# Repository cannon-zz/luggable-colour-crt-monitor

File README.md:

# Colour CRT Monitor for a Retro Luggable Computer

I'm in the process of assembling a luggable Apple ][ clone system.  This is the colour monitor part of the project.

This monitor started out as a SKYTEK brand SCT-1024 portable colour television from May of 1988 that I picked up from an auction site.  The video baseband and CRT driver section is built around a Panasonic 150CHB22 picture tube driven by a Toshiba TA7698AP video-chroma-deflection system all-in-one chip.  I think those picture tubes were quite common in small televisions of this type, and the all-in-one chip is easy to find, so this project might be useful for others looking for a way to make a small DIY CRT colour monitor from salvaged parts.

## Status

- [X] First pass through the circuit, entering it into kicad.
  - CRT socket board not included.  Will reuse as-is.
  - 11 V regulator circuit not included.  Considering alternatives.
- [X] Remove components from PCB, confirm values out-of-circuit.
  - Confirm internal structure of flyback.
  - Identify coils, diodes, capacitors.
- [X] Select new replacement parts.
- [X] Assign footprints.
- [X] Layout PCB.
- [X] Parts and PCBs ordered.
- [ ] Assembled.
- [ ] Tested and working (knock on wood).

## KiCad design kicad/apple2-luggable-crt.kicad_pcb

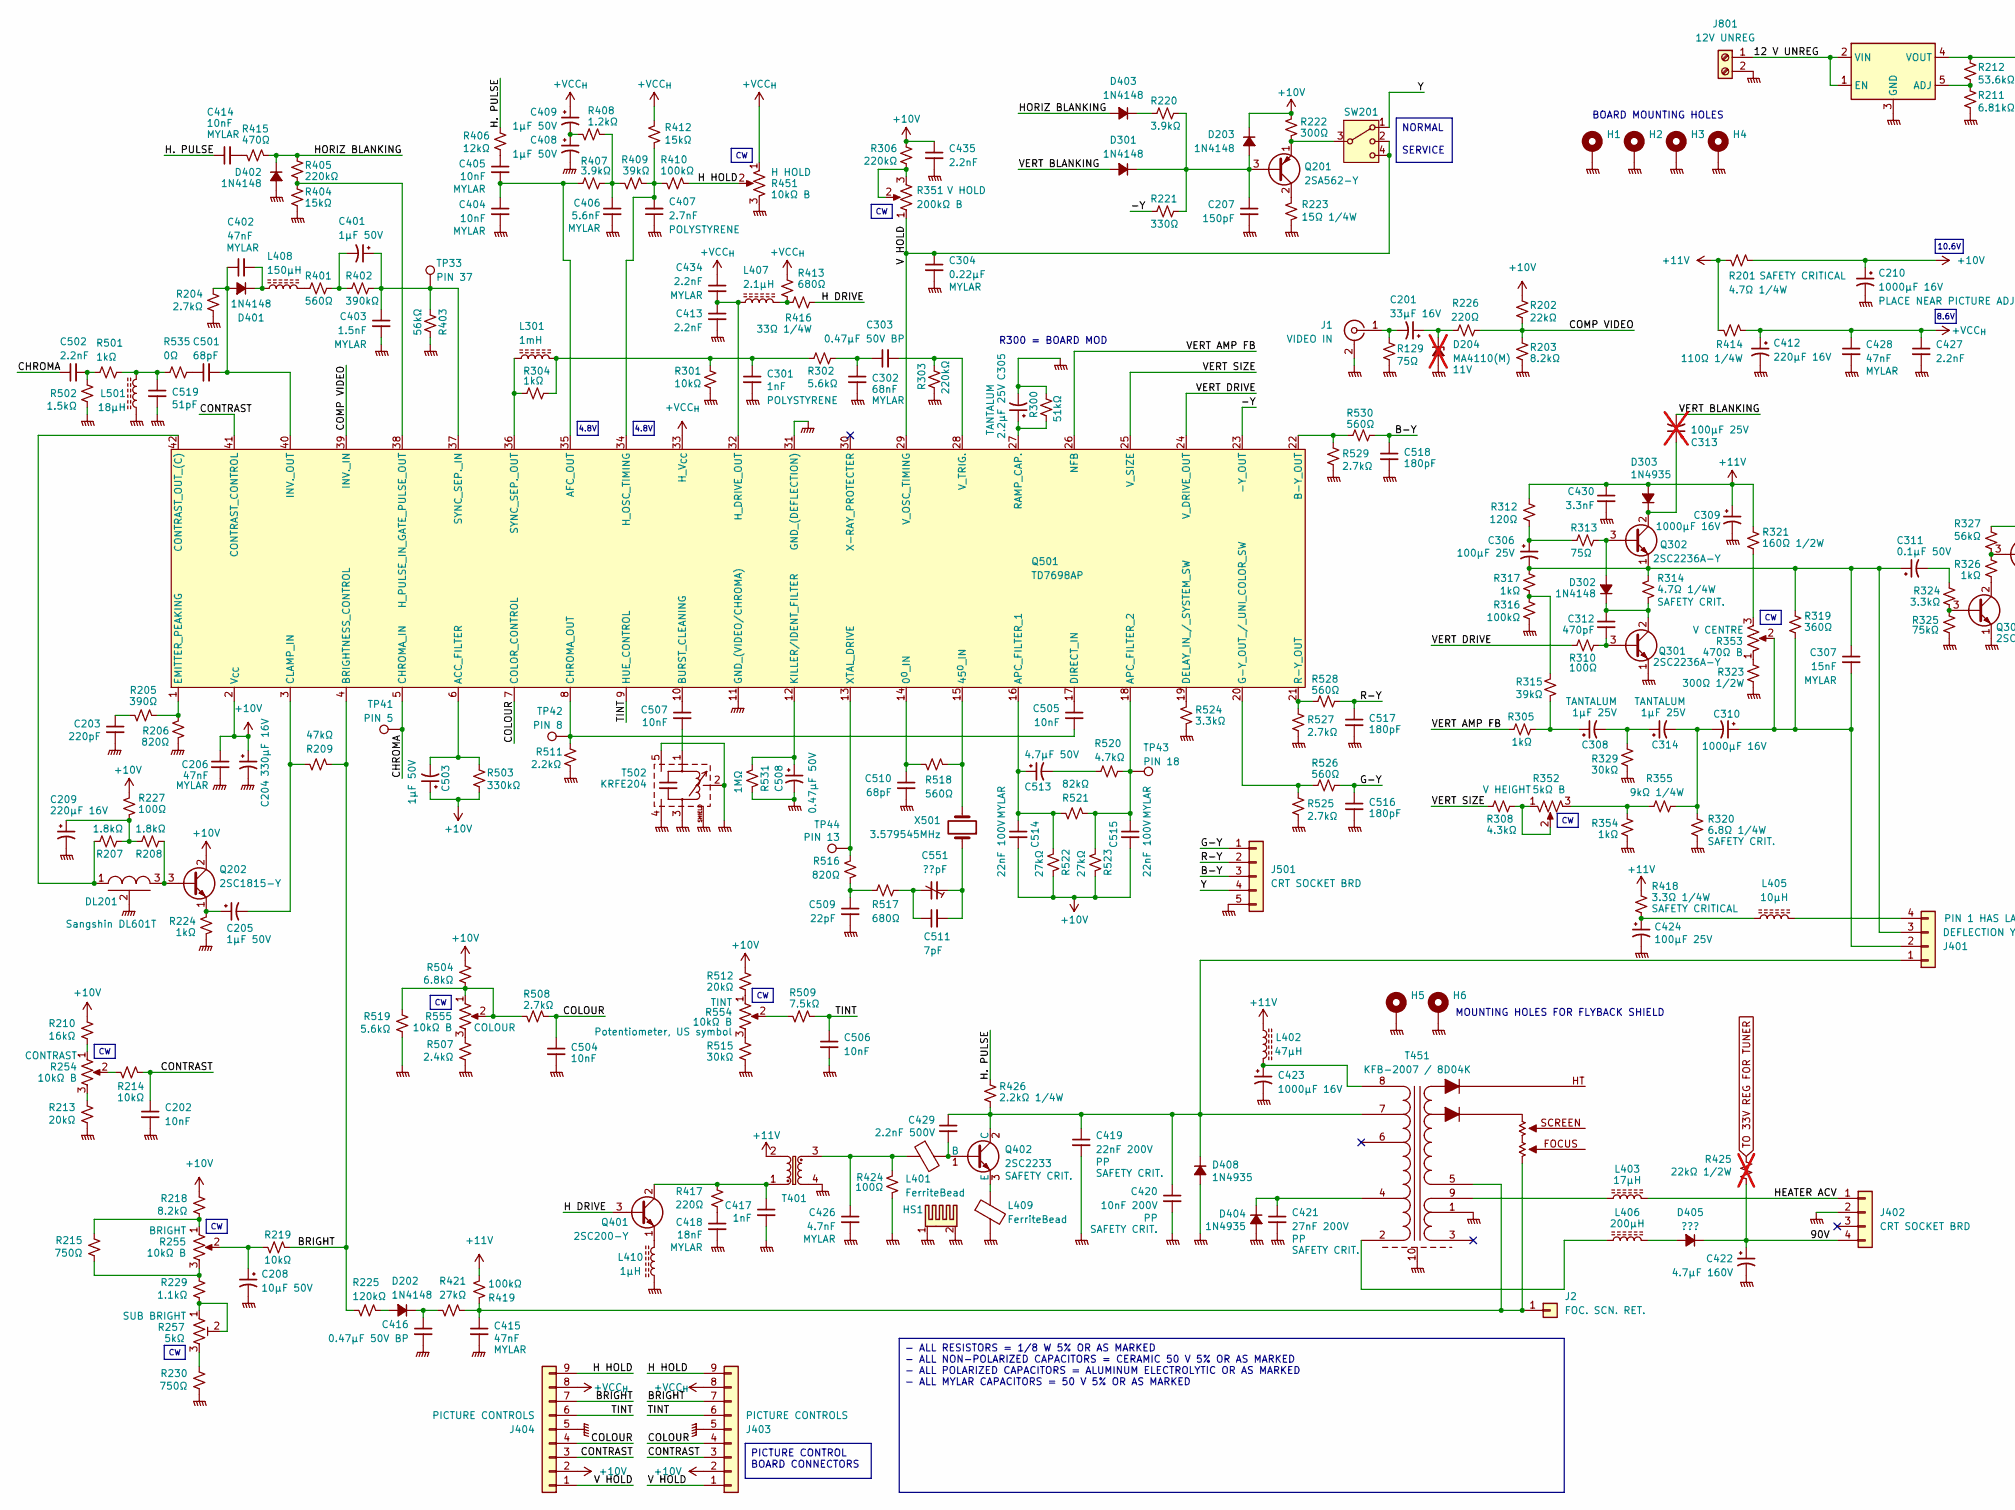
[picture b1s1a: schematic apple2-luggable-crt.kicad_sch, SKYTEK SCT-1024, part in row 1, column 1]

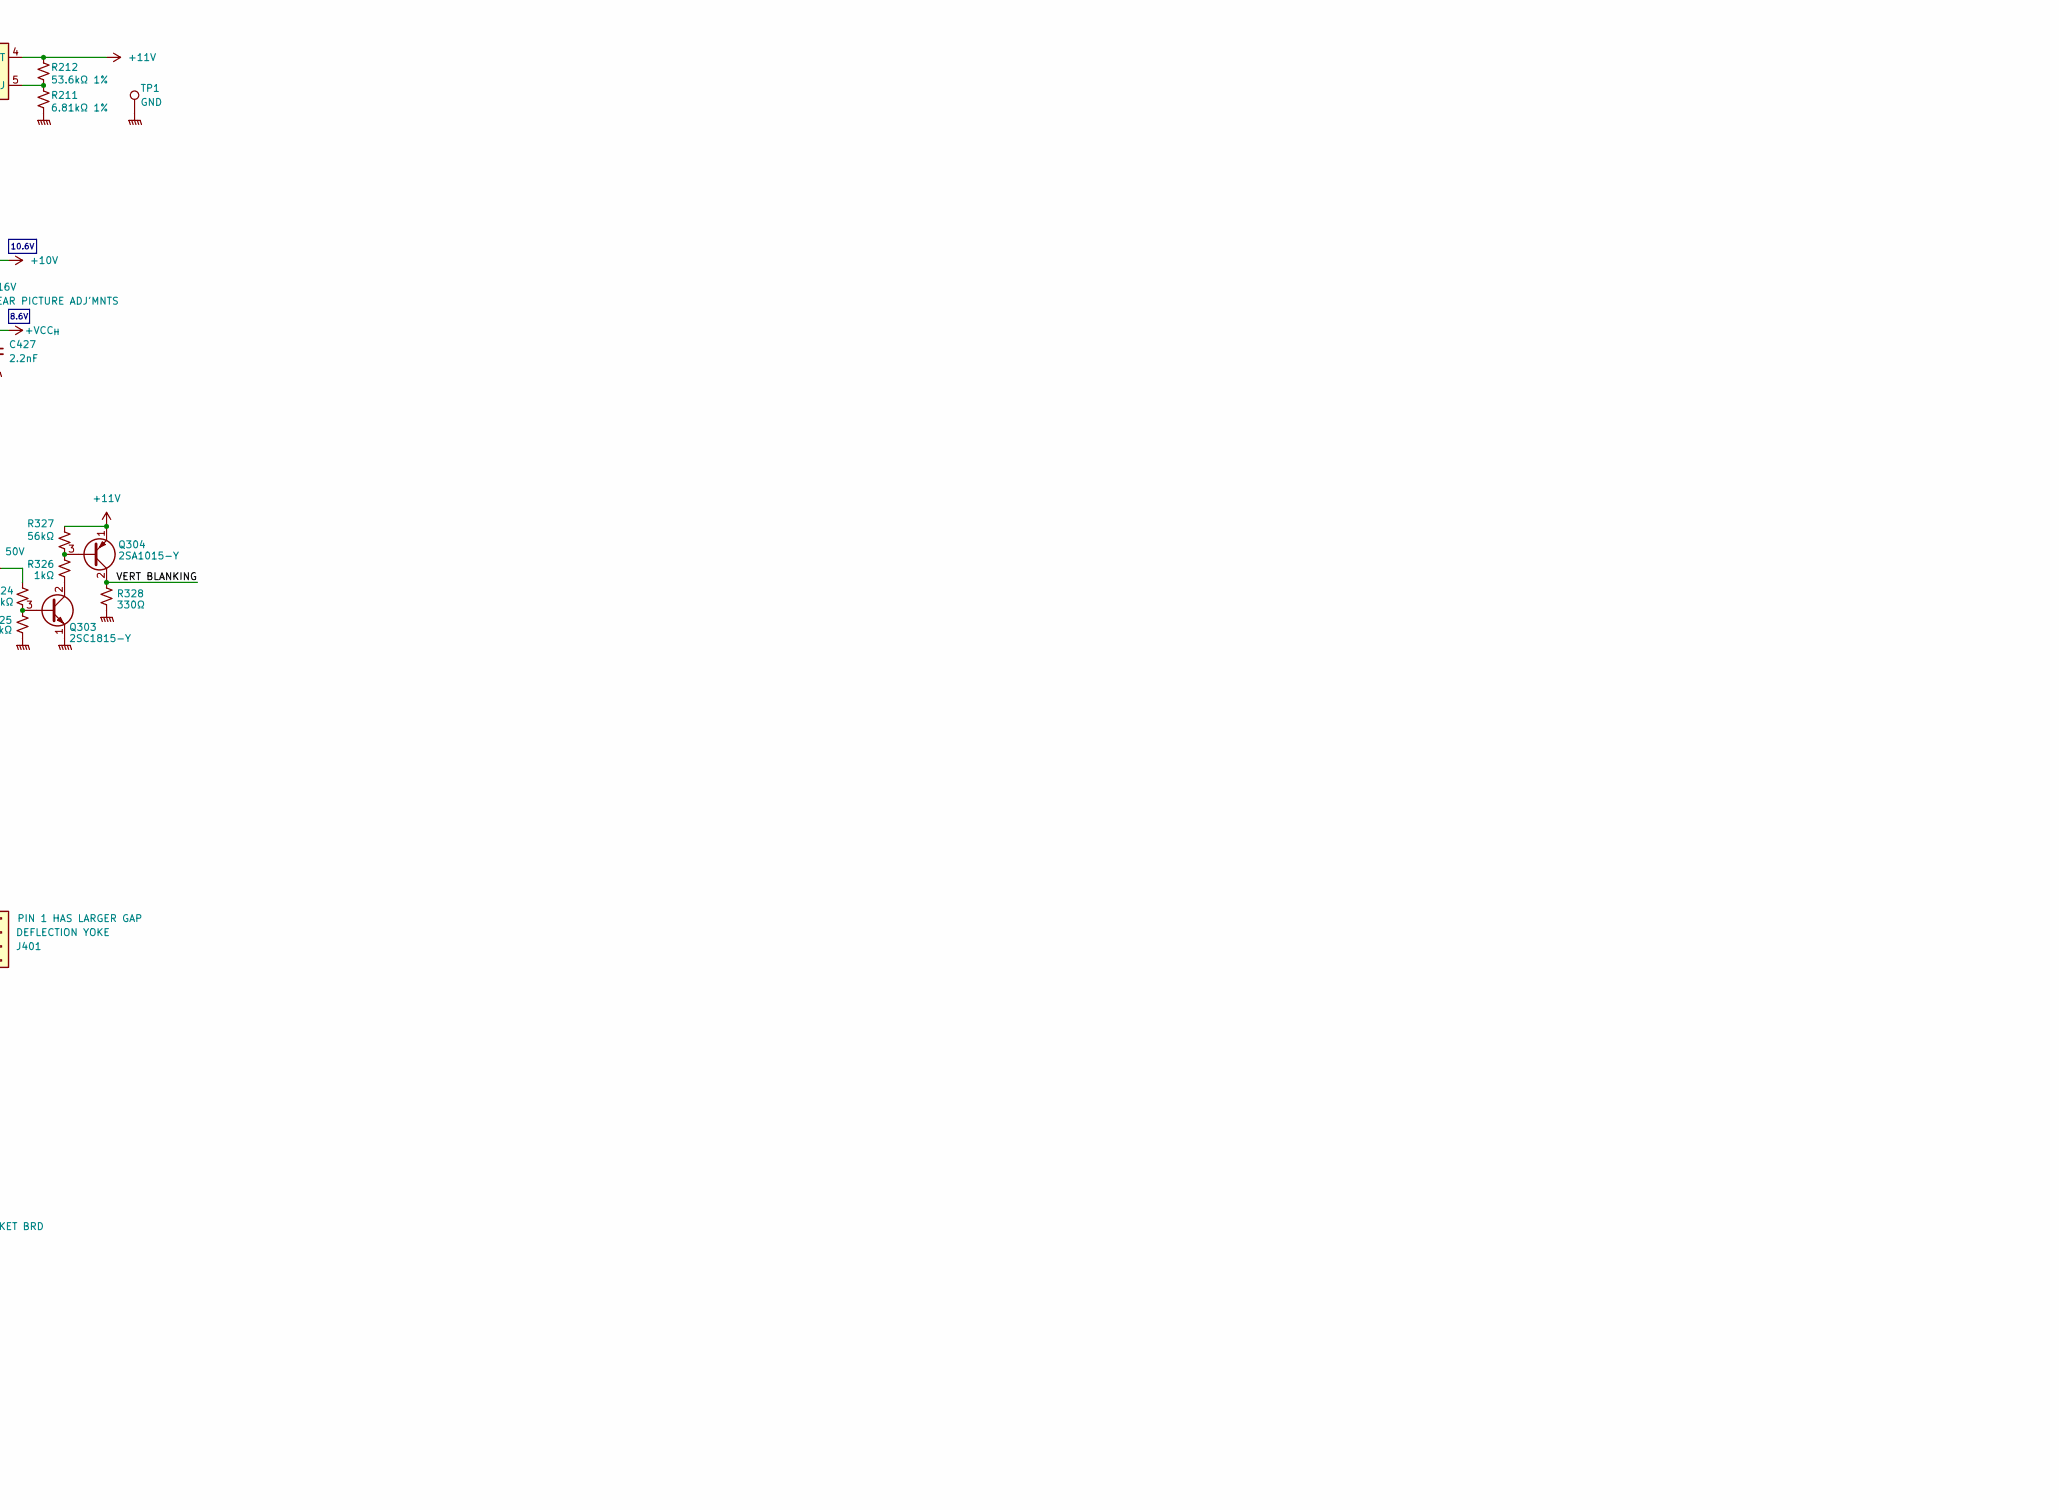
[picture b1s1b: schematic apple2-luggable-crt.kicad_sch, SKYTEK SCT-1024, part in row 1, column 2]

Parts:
C201: 33μF 16V; CP_Radial_D5.0mm_P2.00mm
C202, C404, C405, C414, C504, C505, C506, C507: 10nF; C_0805_2012Metric_Pad1.18x1.45mm_HandSolder
C203: 220pF; C_0805_2012Metric_Pad1.18x1.45mm_HandSolder
C204: 330μF 16V; CP_Radial_D8.0mm_P3.50mm
C205, C401, C408, C409, C503: 1μF 50V; C_0805_2012Metric_Pad1.18x1.45mm_HandSolder
C206, C402, C415, C428: 47nF; C_0805_2012Metric_Pad1.18x1.45mm_HandSolder
C207: 150pF; C_0805_2012Metric_Pad1.18x1.45mm_HandSolder
C208: 10μF 50V; C_0805_2012Metric_Pad1.18x1.45mm_HandSolder
C209, C412: 220μF 16V; CP_Radial_D8.0mm_P3.50mm
C210, C309, C310, C423: 1000μF 16V; CP_Radial_D8.0mm_P3.50mm
C301, C417: 1nF; C_0805_2012Metric_Pad1.18x1.45mm_HandSolder
C302: 68nF; C_0805_2012Metric_Pad1.18x1.45mm_HandSolder
C303, C416: 0.47μF 50V BP; C_0805_2012Metric_Pad1.18x1.45mm_HandSolder
C304: 0.22μF; C_0805_2012Metric_Pad1.18x1.45mm_HandSolder
C305: 2.2μF 25V; C_0805_2012Metric_Pad1.18x1.45mm_HandSolder
C306, C424: 100μF 25V; CP_Radial_D6.3mm_P2.50mm
C307: 15nF; C_0805_2012Metric_Pad1.18x1.45mm_HandSolder
C308, C314: 1μF 25V; C_0805_2012Metric_Pad1.18x1.45mm_HandSolder
C311: 0.1μF 50V; C_0805_2012Metric_Pad1.18x1.45mm_HandSolder
C312: 470pF; C_0805_2012Metric_Pad1.18x1.45mm_HandSolder
C313: 100μF 25V; CP_Radial_D8.0mm_P3.50mm; not fitted
C403: 1.5nF; C_0805_2012Metric_Pad1.18x1.45mm_HandSolder
C406: 5.6nF; C_0805_2012Metric_Pad1.18x1.45mm_HandSolder
C407: 2.7nF; C_0805_2012Metric_Pad1.18x1.45mm_HandSolder
C413, C427, C434, C435, C502: 2.2nF; C_0805_2012Metric_Pad1.18x1.45mm_HandSolder
C418: 18nF; C_0805_2012Metric_Pad1.18x1.45mm_HandSolder
C419: 22nF 200V; C_Rect_L10.3mm_W4.5mm_P7.50mm_MKS4
C420: 10nF 200V; C_Rect_L10.3mm_W4.5mm_P7.50mm_MKS4
C421: 27nF 200V; C_Rect_L10.3mm_W4.5mm_P7.50mm_MKS4
C422: 4.7μF 160V; CP_Radial_D6.3mm_P2.50mm
C426: 4.7nF; C_0805_2012Metric_Pad1.18x1.45mm_HandSolder
C429: 2.2nF 500V; C_0805_2012Metric_Pad1.18x1.45mm_HandSolder
C430: 3.3nF; C_0805_2012Metric_Pad1.18x1.45mm_HandSolder
C501, C510: 68pF; C_0805_2012Metric_Pad1.18x1.45mm_HandSolder
C508: 0.47μF 50V; C_0805_2012Metric_Pad1.18x1.45mm_HandSolder
C509: 22pF; C_0805_2012Metric_Pad1.18x1.45mm_HandSolder
C511: 7pF; C_0805_2012Metric_Pad1.18x1.45mm_HandSolder
C513: 4.7μF 50V; C_0805_2012Metric_Pad1.18x1.45mm_HandSolder
C514, C515: 22nF 100V; C_0805_2012Metric_Pad1.18x1.45mm_HandSolder
C516, C517, C518: 180pF; C_0805_2012Metric_Pad1.18x1.45mm_HandSolder
C519: 51pF; C_0805_2012Metric_Pad1.18x1.45mm_HandSolder
C551: ??pF; C_Rect_L7.0mm_W6.5mm_P5.00mm
D202, D203, D301, D302, D401, D402, D403: 1N4148; D_MiniMELF_Handsoldering
D204: MA4110(M); not fitted
D303, D404, D408: 1N4935; D_DO-41_SOD81_P10.16mm_Horizontal
D405: ???; D_DO-41_SOD81_P10.16mm_Horizontal
DL201: Sangshin DL601T; DelayLine_Sangshin_DL601T
H1, H2, H3, H4: M4; MountingHole_4.3mm_M4_Pad_TopBottom
H5, H6: M3; MountingHole_3.2mm_M3_Pad_TopBottom_flyback_shield
HS1: Heatsink_Pad_2Pin; Heatsink_TO-220_26x20mm_2xFixation1.2mm
J1: VIDEO IN; BNC_TEConnectivity_1478204_Vertical
J2: FOC. SCN. RET.; PinHeader_1x01_P2.54mm_Vertical
J401: DEFLECTION YOKE; DEFLECTION_CONNECTOR
J402: CRT SOCKET BRD; JST_XH_B4B-XH-A_1x04_P2.50mm_Vertical
J403, J404: PICTURE CONTROLS; JST_PH_B9B-PH-K_1x09_P2.00mm_Vertical
J501: CRT SOCKET BRD; JST_XH_B5B-XH-A_1x05_P2.50mm_Vertical
J801: 12V UNREG; JST_VH_B2P-VH_1x02_P3.96mm_Vertical
L301: 1mH; L_1008_2520Metric_Pad1.43x2.20mm_HandSolder
L401, L409: FerriteBead; Ferrite_L12.0mm_D3.2mm_P18.0mm_Horizontal
L402: 47μH; L_Radial_D7.8mm_P5.00mm_Fastron_07HCP
L403: 17μH; L_Radial_D6.0mm_P8.00mm
L405: 10μH; L_Radial_D10.0mm_P7.62mm
L406: 200μH; L_Radial_D7.5mm_P5.00mm_Fastron_07P
L407: 2.1μH; L_Radial_D7.5mm_P5.00mm_Fastron_07P
L408: 150μH; L_TDK_NLV32_3.2x2.5mm
L410: 1μH; L_Radial_D7.5mm_P5.00mm_Fastron_07P
L501: 18μH; L_TDK_NLV32_3.2x2.5mm
Q201: 2SA562-Y; TO-92_Inline_Wide
Q202, Q303: 2SC1815-Y; TO-92_Inline_Wide
Q301, Q302: 2SC2236A-Y; TO-92_Inline_Wide
Q304: 2SA1015-Y; TO-92_Inline_Wide
Q401: 2SC200-Y; TO-92_Inline_Wide
Q402: 2SC2233; TO-220-3_Vertical
Q501: TD7698AP; DIP-42_W15.24mm_LongPads
R129, R313: 75Ω; R_1206_3216Metric_Pad1.30x1.75mm_HandSolder
R201, R314: 4.7Ω 1/4W; R_Axial_DIN0207_L6.3mm_D2.5mm_P15.24mm_Horizontal
R202: 22kΩ; R_1206_3216Metric_Pad1.30x1.75mm_HandSolder
R203, R218: 8.2kΩ; R_1206_3216Metric_Pad1.30x1.75mm_HandSolder
R204, R508, R525, R527, R529: 2.7kΩ; R_1206_3216Metric_Pad1.30x1.75mm_HandSolder
R205: 390Ω; R_1206_3216Metric_Pad1.30x1.75mm_HandSolder
R206, R516: 820Ω; R_1206_3216Metric_Pad1.30x1.75mm_HandSolder
R207, R208: 1.8kΩ; R_1206_3216Metric_Pad1.30x1.75mm_HandSolder
R209: 47kΩ; R_1206_3216Metric_Pad1.30x1.75mm_HandSolder
R210: 16kΩ; R_1206_3216Metric_Pad1.30x1.75mm_HandSolder
R211: 6.81kΩ 1%; R_1206_3216Metric_Pad1.30x1.75mm_HandSolder
R212: 53.6kΩ 1%; R_1206_3216Metric_Pad1.30x1.75mm_HandSolder
R213, R512: 20kΩ; R_1206_3216Metric_Pad1.30x1.75mm_HandSolder
R214, R219, R301: 10kΩ; R_1206_3216Metric_Pad1.30x1.75mm_HandSolder
R215, R230: 750Ω; R_1206_3216Metric_Pad1.30x1.75mm_HandSolder
R220, R407: 3.9kΩ; R_1206_3216Metric_Pad1.30x1.75mm_HandSolder
R221, R328: 330Ω; R_1206_3216Metric_Pad1.30x1.75mm_HandSolder
R222: 300Ω; R_1206_3216Metric_Pad1.30x1.75mm_HandSolder
R223: 15Ω 1/4W; R_1206_3216Metric_Pad1.30x1.75mm_HandSolder
R224, R304, R305, R317, R326, R354, R501: 1kΩ; R_1206_3216Metric_Pad1.30x1.75mm_HandSolder
R225: 120kΩ; R_1206_3216Metric_Pad1.30x1.75mm_HandSolder
R226, R417: 220Ω; R_1206_3216Metric_Pad1.30x1.75mm_HandSolder
R227, R310, R424: 100Ω; R_1206_3216Metric_Pad1.30x1.75mm_HandSolder
R229: 1.1kΩ; R_1206_3216Metric_Pad1.30x1.75mm_HandSolder
R254, R255, R451, R554, R555: 10kΩ B; Potentiometer_Alpha_RD901F-40-00D_Single_Vertical_CircularH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
R257: 5kΩ; Potentiometer_Bourns_3386F_Vertical
R300: 51kΩ; R_1206_3216Metric_Pad1.30x1.75mm_HandSolder
R302, R519: 5.6kΩ; R_1206_3216Metric_Pad1.30x1.75mm_HandSolder
R303, R306, R405: 220kΩ; R_1206_3216Metric_Pad1.30x1.75mm_HandSolder
R308: 4.3kΩ; R_1206_3216Metric_Pad1.30x1.75mm_HandSolder
R312: 120Ω; R_1206_3216Metric_Pad1.30x1.75mm_HandSolder
R315, R409: 39kΩ; R_1206_3216Metric_Pad1.30x1.75mm_HandSolder
R316, R410, R419: 100kΩ; R_1206_3216Metric_Pad1.30x1.75mm_HandSolder
R319: 360Ω; R_1206_3216Metric_Pad1.30x1.75mm_HandSolder
R320: 6.8Ω 1/4W; R_Axial_DIN0207_L6.3mm_D2.5mm_P15.24mm_Horizontal
R321: 160Ω 1/2W; R_1206_3216Metric_Pad1.30x1.75mm_HandSolder
R323: 300Ω 1/2W; R_1206_3216Metric_Pad1.30x1.75mm_HandSolder
R324, R524: 3.3kΩ; R_1206_3216Metric_Pad1.30x1.75mm_HandSolder
R325: 75kΩ; R_1206_3216Metric_Pad1.30x1.75mm_HandSolder
R327, R403: 56kΩ; R_1206_3216Metric_Pad1.30x1.75mm_HandSolder
R329, R515: 30kΩ; R_1206_3216Metric_Pad1.30x1.75mm_HandSolder
R351: 200kΩ B; Potentiometer_Alpha_RD901F-40-00D_Single_Vertical_CircularH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
R352: 5kΩ B; Potentiometer_Bourns_3386F_Vertical
R353: 470Ω B; Potentiometer_Bourns_3386F_Vertical
R355: 9kΩ 1/4W; R_1206_3216Metric_Pad1.30x1.75mm_HandSolder
R401, R518, R526, R528, R530: 560Ω; R_1206_3216Metric_Pad1.30x1.75mm_HandSolder
R402: 390kΩ; R_1206_3216Metric_Pad1.30x1.75mm_HandSolder
R404, R412: 15kΩ; R_1206_3216Metric_Pad1.30x1.75mm_HandSolder
R406: 12kΩ; R_1206_3216Metric_Pad1.30x1.75mm_HandSolder
R408: 1.2kΩ; R_1206_3216Metric_Pad1.30x1.75mm_HandSolder
R413, R517: 680Ω; R_1206_3216Metric_Pad1.30x1.75mm_HandSolder
R414: 110Ω 1/4W; R_1206_3216Metric_Pad1.30x1.75mm_HandSolder
R415: 470Ω; R_1206_3216Metric_Pad1.30x1.75mm_HandSolder
R416: 33Ω 1/4W; R_1206_3216Metric_Pad1.30x1.75mm_HandSolder
R418: 3.3Ω 1/4W; R_Axial_DIN0207_L6.3mm_D2.5mm_P15.24mm_Horizontal
R421, R522, R523: 27kΩ; R_1206_3216Metric_Pad1.30x1.75mm_HandSolder
R425: 22kΩ 1/2W; not fitted
R426: 2.2kΩ 1/4W; R_1206_3216Metric_Pad1.30x1.75mm_HandSolder
R502: 1.5kΩ; R_1206_3216Metric_Pad1.30x1.75mm_HandSolder
R503: 330kΩ; R_1206_3216Metric_Pad1.30x1.75mm_HandSolder
R504: 6.8kΩ; R_1206_3216Metric_Pad1.30x1.75mm_HandSolder
R507: 2.4kΩ; R_1206_3216Metric_Pad1.30x1.75mm_HandSolder
R509: 7.5kΩ; R_1206_3216Metric_Pad1.30x1.75mm_HandSolder
R511: 2.2kΩ; R_1206_3216Metric_Pad1.30x1.75mm_HandSolder
R520: 4.7kΩ; R_1206_3216Metric_Pad1.30x1.75mm_HandSolder
R521: 82kΩ; R_1206_3216Metric_Pad1.30x1.75mm_HandSolder
R531: 1MΩ; R_1206_3216Metric_Pad1.30x1.75mm_HandSolder
R535: 0Ω; R_1206_3216Metric_Pad1.30x1.75mm_HandSolder
SW201: SW_SP3T; SW_SERVICE
T401: L_Ferrite_Coupled_1243; Transformer_Horiz_Drive
T451: KFB-2007 / 8D04K; Flyback
T502: KRFE204; CHROMA_FILTER
TP1: GND; TestPoint_THTPad_D3.0mm_Drill1.5mm
TP33: PIN 37; TestPoint_THTPad_D3.0mm_Drill1.5mm
TP41: PIN 5; TestPoint_THTPad_D3.0mm_Drill1.5mm
TP42: PIN 8; TestPoint_THTPad_D3.0mm_Drill1.5mm
TP43: PIN 18; TestPoint_THTPad_D3.0mm_Drill1.5mm
TP44: PIN 13; TestPoint_THTPad_D3.0mm_Drill1.5mm
U1: XRP29302ETBTR-L; TO-263-5_TabPin3
X501: 3.579545MHz; Crystal_HC49-U_Vertical

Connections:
+10V: C204.1, C206.1, C210.1, C435.1, C503.1, C514.2, C515.2, D203.1 (K), J403.2, J404.2, Q202.2 (C), Q501.2 (V_{CC}), R201.2, R202.1, R210.1, R218.1, R222.2, R227.2, R306.2, R503.2, R504.1, R512.1, R522.2, R523.2
+11V: C309.1, C430.1, D303.2 (A), L402.1, Q304.1 (E), R201.1, R212.1, R312.1, R321.1, R327.1, R414.2, R418.2, R419.2, T401.2, U1.4 (VOUT)
+VCC_{H}: C409.1, C412.1, C427.1, C428.1, C434.1, J403.8, J404.8, Q501.33 (H_V_{CC}), R412.1, R413.2, R414.1, R451.1
/12 V UNREG: J801.1, U1.1 (EN), U1.2 (VIN)
/90V: C422.1, D405.1 (K), J402.4, R425.1
/-Y: Q501.23 (-Y_OUT), R221.1
/B-Y: C518.1, J501.3, R530.2
/BRIGHT: J403.7, J404.7, Q501.4 (BRIGHTNESS_CONTROL), R209.2, R219.1, R225.2
/CHROMA: C502.1, Q501.5 (CHROMA_IN), TP41.1 (1_1)
/COLOUR: C504.1, J403.4, J404.4, Q501.7 (COLOR_CONTROL), R508.1
/COMP VIDEO: Q501.39 (INV._IN), R202.2, R203.1, R226.1
/CONTRAST: C202.1, J403.3, J404.3, Q501.41 (CONTRAST_CONTROL), R214.1
/G-Y: C516.1, J501.1, R526.2
/H DRIVE: Q401.3 (B), R416.2
/H HOLD: J403.9, J404.9, R410.1, R451.2
/H. PULSE: C414.1, R406.2, R426.2
/HEATER ACV: J402.1, L403.2
/HORIZ BLANKING: D402.1 (K), D403.2 (A), R405.2, R415.1
/R-Y: C517.1, J501.2, R528.2
/TINT: C506.1, J403.6, J404.6, Q501.9 (HUE_CONTROL), R509.1
/V HOLD: C304.1, J403.1, J404.1, Q501.29 (V_OSC_TIMING), R351.1, SW201.2, SW201.4
/VERT AMP FB: Q501.26 (NFB), R305.1
/VERT BLANKING: C313.2, D301.2 (A), Q304.2 (C), R328.1
/VERT DRIVE: Q501.24 (V_DRIVE_OUT), R310.1
/VERT SIZE: Q501.25 (V_SIZE), R308.1
/Y: J501.4, SW201.1
GNDPWR: C202.2, C203.2, C204.2, C206.2, C207.2, C208.2, C209.2, C210.2, C301.2, C302.2, C304.2, C305.2, C309.2, C403.2, C404.2, C406.2, C407.1, C408.2, C412.2, C413.2, C415.2, C416.2, C417.2, C418.2, C419.2, C420.2, C421.2, C422.2, C423.2, C424.2, C426.2, C427.2, C428.2, C430.2, C435.2, C504.2, C506.2, C508.2, C509.2, C510.2, C516.2, C517.2, C518.2, C519.2, D204.2 (A), D402.2 (A), D404.2 (A), D408.2 (A), DL201.2 (COMMUN), H1.1 (1_1), H2.1 (1_1), H3.1 (1_1), H4.1 (1_1), H5.1 (1_1), H6.1 (1_1), HS1.1, HS1.2, J1.2 (Ext), J402.2, J403.5, J404.5, J501.5, J801.2, L409.2, L410.2, L501.1, Q301.1 (E), Q303.1 (E), Q501.11 (GND_(VIDEO/CHROMA)), Q501.31 (GND_(DEFLECTION)), R129.2, R203.2, R204.2, R206.2, R211.2, R213.2, R223.1, R224.2, R230.2, R300.2, R301.1, R303.1, R316.2, R320.2, R323.2, R325.2, R328.2, R329.2, R354.2, R403.2, R404.2, R424.1, R451.3, R502.2, R507.2, R511.2, R515.2, R519.2, R524.2, R525.2, R527.2, R529.2, R531.2, T401.4, T451.1 (HEATER), T451.10, T502.2, T502.3, T502.4, T502.5, T502.SHIELD, TP1.1 (1_1), U1.3 (GND)
unnamed: C201.1, D204.1 (K), R226.2
unnamed: C203.1, R205.2
unnamed: C208.1, R219.2, R255.2
unnamed: C209.1, R207.1, R208.2, R227.1
unnamed: C301.1, L301.1, R301.2, R302.1, R304.1
unnamed: C302.1, C303.1, R302.2
unnamed: C306.1, R312.2, R313.1
unnamed: C308.1, R305.2, R315.2
unnamed: C308.2, C314.1, R329.1
unnamed: C310.2, C314.2, R320.1, R355.2
unnamed: C311.2, R324.2
unnamed: C401.2, R401.2, R402.1
unnamed: C405.1, R406.1
unnamed: C406.1, R407.2, R408.1, R409.2
unnamed: C408.1, C409.2, R408.2
unnamed: C414.2, R415.2
unnamed: C418.1, R417.1
unnamed: C423.1, L402.2, T451.8
unnamed: C424.1, L405.1, R418.1
unnamed: C426.1, L401.1, R424.2, T401.3
unnamed: C501.1, R535.1
unnamed: C502.2, R501.2, R502.1
unnamed: C507.2, T502.1
unnamed: C509.1, R516.2, R517.1
unnamed: C511.1, C551.2, R517.2
unnamed: C511.2, C551.1, X501.1
unnamed: C513.2, R520.1
unnamed: C519.1, L501.2, R501.1, R535.2
unnamed: D202.2 (A), R225.1
unnamed: C416.1, D202.1 (K), R421.1
unnamed: C207.1, D203.2 (A), D301.1 (K), Q201.3 (B), R220.2, R221.2
unnamed: D302.2 (A), Q302.3 (B), R313.2
unnamed: C312.1, D302.1 (K), Q301.2 (C), R314.2
unnamed: C313.1, D303.1 (K), Q302.2 (C)
unnamed: C402.1, C501.2, D401.2 (A), Q501.40 (INV._OUT), R204.1
unnamed: C402.2, D401.1 (K), L408.2
unnamed: D403.1 (K), R220.1
unnamed: C421.1, D404.1 (K), T451.4
unnamed: D405.2 (A), L406.2
unnamed: C419.1, C420.1, C429.1, D408.1 (K), J401.1, Q402.2 (C), R426.1, T451.7
unnamed: C201.2, J1.1 (In), R129.1
unnamed: C415.1, J2.1 (Pin_1_1), R419.1, R421.2, T451., T451.5
unnamed: C307.2, C310.1, J401.2, R319.2, R353.2
unnamed: C306.2, C307.1, C311.1, J401.3, Q302.1 (E), R314.1, R317.2, R319.1
unnamed: J401.4, L405.2
unnamed: L403.1, T451.9 (HEATER)
unnamed: L406.1, T451.2
unnamed: L407.1, R413.1, R416.1
unnamed: L408.1, R401.1
unnamed: Q201.2 (C), R223.2
unnamed: Q201.1 (E), R222.1, SW201.3
unnamed: DL201.3, Q202.3 (B), R208.1
unnamed: C205.1, Q202.1 (E), R224.1
unnamed: C312.2, Q301.3 (B), R310.2
unnamed: Q303.3 (B), R324.1, R325.1
unnamed: Q303.2 (C), R326.1
unnamed: Q304.3 (B), R326.2, R327.2
unnamed: C417.1, Q401.2 (C), R417.2, T401.1
unnamed: L410.1, Q401.1 (E)
unnamed: C429.2, L401.2, Q402.1 (B)
unnamed: L409.1, Q402.3 (E)
unnamed: C510.1, Q501.14 (0^{O}_IN), R518.1
unnamed: Q501.15 (45^{O}_IN), R518.2, X501.2
unnamed: C503.2, Q501.6 (ACC_FILTER), R503.1
unnamed: C404.1, C405.2, Q501.35 (AFC_OUT), R407.1
unnamed: C513.1, C514.1, Q501.16 (APC_FILTER_1), R521.1, R522.1
unnamed: C515.1, Q501.18 (APC_FILTER_2), R520.2, R521.2, R523.1, TP43.1 (1_1)
unnamed: Q501.22 (B-Y_OUT), R529.1, R530.1
unnamed: C507.1, Q501.10 (BURST_CLEANING)
unnamed: C505.2, Q501.8 (CHROMA_OUT), R511.1, TP42.1 (1_1)
unnamed: C205.2, Q501.3 (CLAMP_IN), R209.1
unnamed: DL201.1, Q501.42 (CONTRAST_OUT_(C)), R207.2
unnamed: Q501.19 (DELAY_IN_/_SYSTEM_SW), R524.1
unnamed: C505.1, Q501.17 (DIRECT_IN)
unnamed: Q501.1 (EMITTER_PEAKING), R205.1, R206.1
unnamed: Q501.20 (G-Y_OUT_/_UNI_COLOR_SW), R525.1, R526.1
unnamed: C413.1, C434.2, L407.2, Q501.32 (H_DRIVE_OUT)
unnamed: C407.2, Q501.34 (H_OSC_TIMING), R409.1, R410.2, R412.2
unnamed: Q501.38 (H_PULSE_IN_GATE_PULSE_OUT), R404.1, R405.1
unnamed: C508.1, Q501.12 (KILLER/IDENT_FILTER), R531.1
unnamed: Q501.21 (R-Y_OUT), R527.1, R528.1
unnamed: C305.1, Q501.27 (RAMP_CAP.), R300.1
unnamed: C401.1, C403.1, Q501.37 (SYNC_SEP._IN), R402.2, R403.1, TP33.1 (1_1)
unnamed: L301.2, Q501.36 (SYNC_SEP._OUT), R304.2
unnamed: C303.2, Q501.28 (V_TRIG.), R303.2
unnamed: Q501.13 (XTAL_DRIVE), R516.1, TP44.1 (1_1)
unnamed: R210.2, R254.1
unnamed: R213.1, R254.3
unnamed: R214.2, R254.2
unnamed: R215.1, R218.2, R255.1
unnamed: R215.2, R229.1, R255.3
unnamed: R229.2, R257.1, R257.2
unnamed: R230.1, R257.3
unnamed: R306.1, R351.2, R351.3
unnamed: R308.2, R352.1, R352.2
unnamed: R315.1, R316.1, R317.1
unnamed: R321.2, R353.3
unnamed: R323.1, R353.1
unnamed: R352.3, R354.1, R355.1
unnamed: R504.2, R508.2, R519.1, R555.1, R555.2
unnamed: R507.1, R555.3
unnamed: R509.2, R554.2
unnamed: R512.2, R554.1
unnamed: R515.1, R554.3
unnamed: R211.1, R212.2, U1.5 (ADJ)

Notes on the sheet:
BOARD MOUNTING HOLES
R300 = BOARD MOD
MOUNTING HOLES FOR FLYBACK SHIELD
10.6V
4.8V
PICTURE CONTROL BOARD CONNECTORS
8.6V
NORMAL SERVICE
- ALL RESISTORS = 1/8 W 5% OR AS MARKED - ALL NON-POLARIZED CAPACITORS = CERAMIC 50 V 5% OR AS MARKED - ALL POLARIZED CAPACITORS = ALUMINUM ELECTROLYTIC OR AS MARKED - ALL MYLAR CAPACITORS = 50 V 5% OR AS MARKED

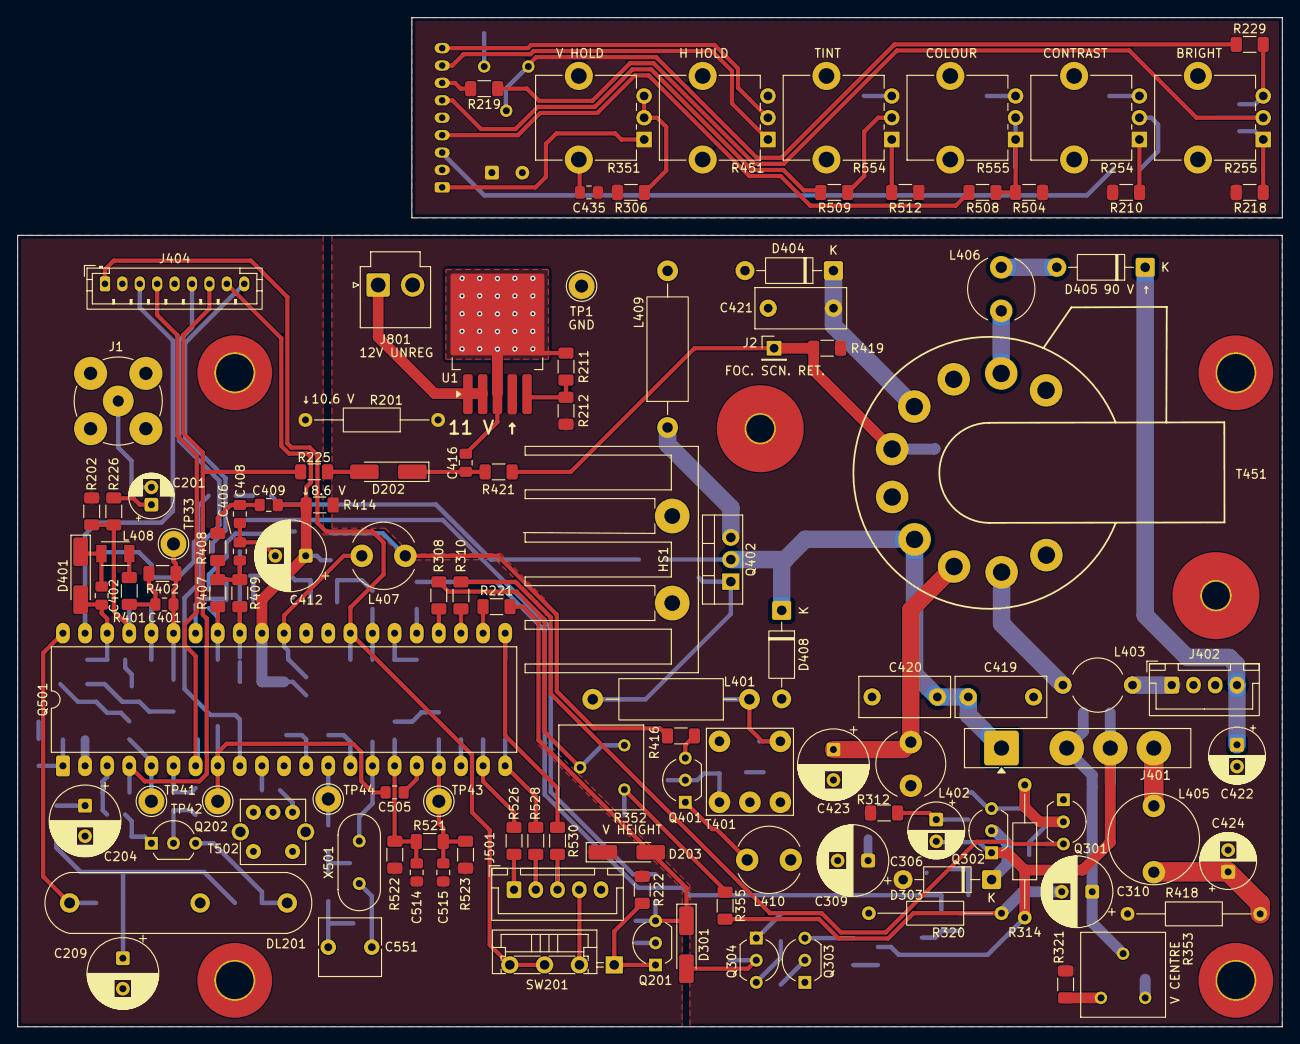
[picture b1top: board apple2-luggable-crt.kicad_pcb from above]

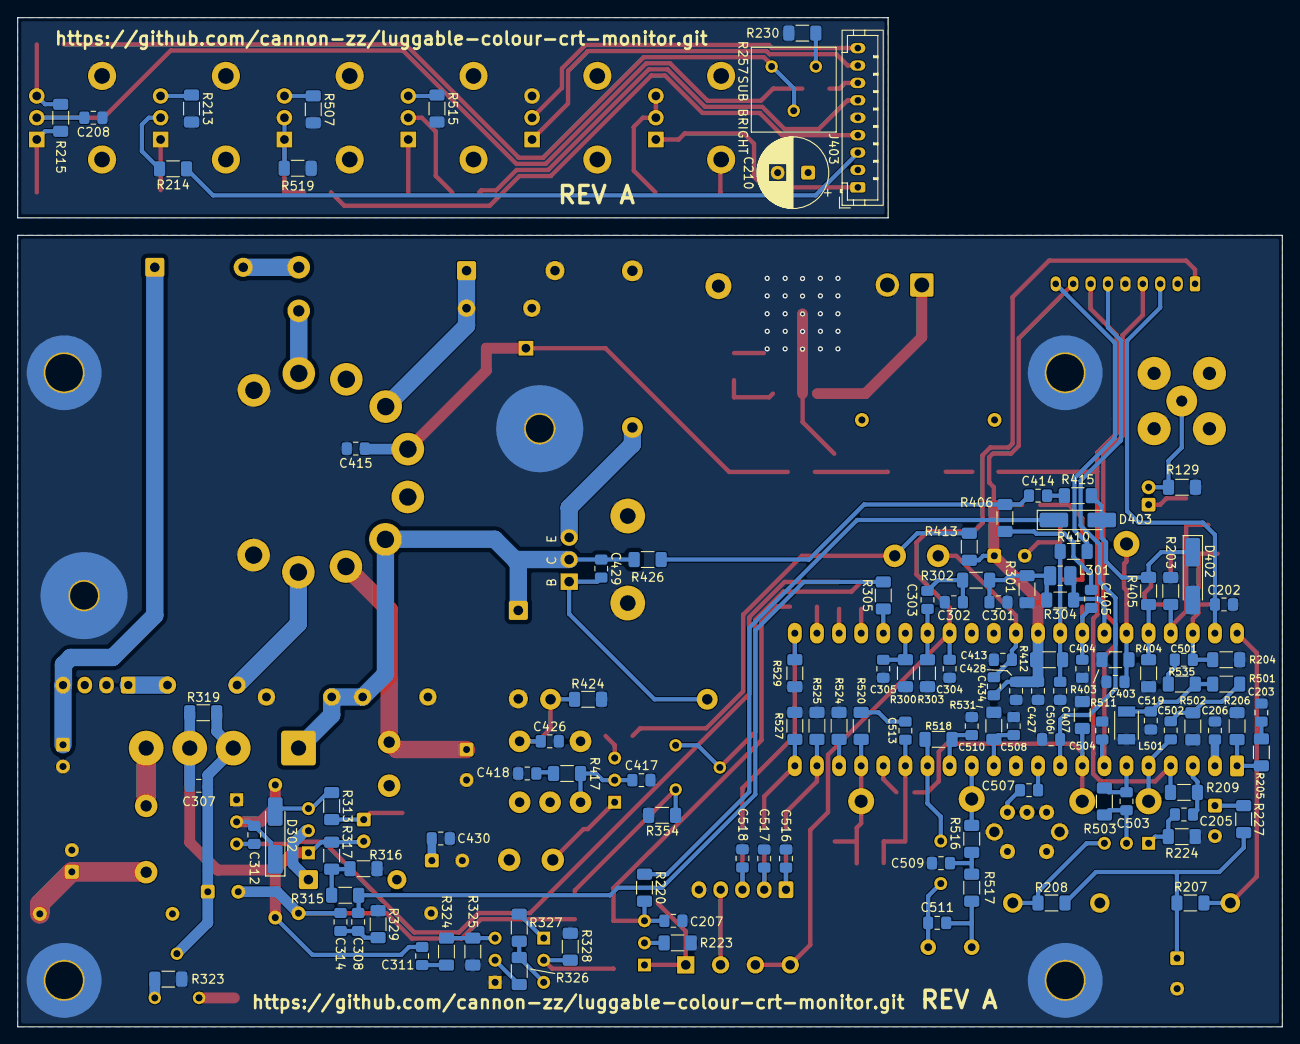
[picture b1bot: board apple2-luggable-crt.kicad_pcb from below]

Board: 2 copper layers, 145.3 x 115.9 mm, 242 parts (117 on the bottom side), 132 nets.

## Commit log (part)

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2026-02-18 add .gitignore
2026-02-18 reorganize filesystem
2026-02-19 add README.md
2026-02-19 add pin 10 to the flyback
2026-02-19 correct voltage of external power brick
2026-02-19 edit README.md
2026-02-19 move notes and reminders out of README.md to notes.md
2026-02-19 README.md: add original manufacture date
2026-02-19 work on flyback internal structure
    - move pins around based on resistance measurements.
2026-02-21 compress the schematic layout somewhat
    - page size is currently A4. I think I can get it down to A3 if I squeeze things around. we'll see.
2026-02-22 start assigning footprints
2026-02-22 edit notes.md
2026-02-22 more work on foot prints
2026-02-23 more progress
    - more foot prints
    - fixed some errors (there was an inductor I had missed altogether)
    - figured out all the inductor values
    - figured out, more or less, most of the diodes
    - rearranged things to squeeze it onto an A3 sheet. when printed onto A4, the components are more compactly arranged but individually larger, and the component values are easier to read.
2026-02-24 more progress
    - more foot prints
    - fix one of the diodes (turns out not to be a zener)
2026-02-24 notes.md: fix some formatting
2026-02-25 more progress
2026-02-26 more progress
    - correct some footprints
2026-02-27 more progress
    - add notes about inductors
    - label the orientations of most variable resistors
    - fix a few other issues here and there
2026-03-01 more progress
    - completed confirming all components out of circuit
    - fixed several errors and omissions
2026-05-05 more work
